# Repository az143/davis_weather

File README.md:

this repository contains all tools necessary for building remote AND online
weather stations using davis vantage vue (or vantage pro) kit.

to be precise, this includes:

* an implementation of the workaround for the infamous "green dot" vendor
lock-in, written in C for a Microchip pic16f88 (without any external
components),

* a data gatherer program (in perl) that fetches the weather readings from a
davis console at configurable intervals, then condenses and uploads the
data to a server on the net,

* a data collector program (in perl) that listens for such uploads and saves the
data in an sqlite database, and optionally uploads it to weather underground
and/or the bom/uk-metoffice weather observations website,

* and a graph generator tool (using gnuplot) and a cgi script to
present readings and graphs. both are written in perl.

there is a little bit of extra documentation on my site at
[http://snafu.priv.at/mystuff/fidobeagle.html](http://snafu.priv.at/mystuff/fidobeagle.html).

all code is (c) 2015 Alexander Zangerl <az@snafu.priv.at>,
and is free and open-source software, licensed under the GPL Version 2.

share and enjoy `:-)`

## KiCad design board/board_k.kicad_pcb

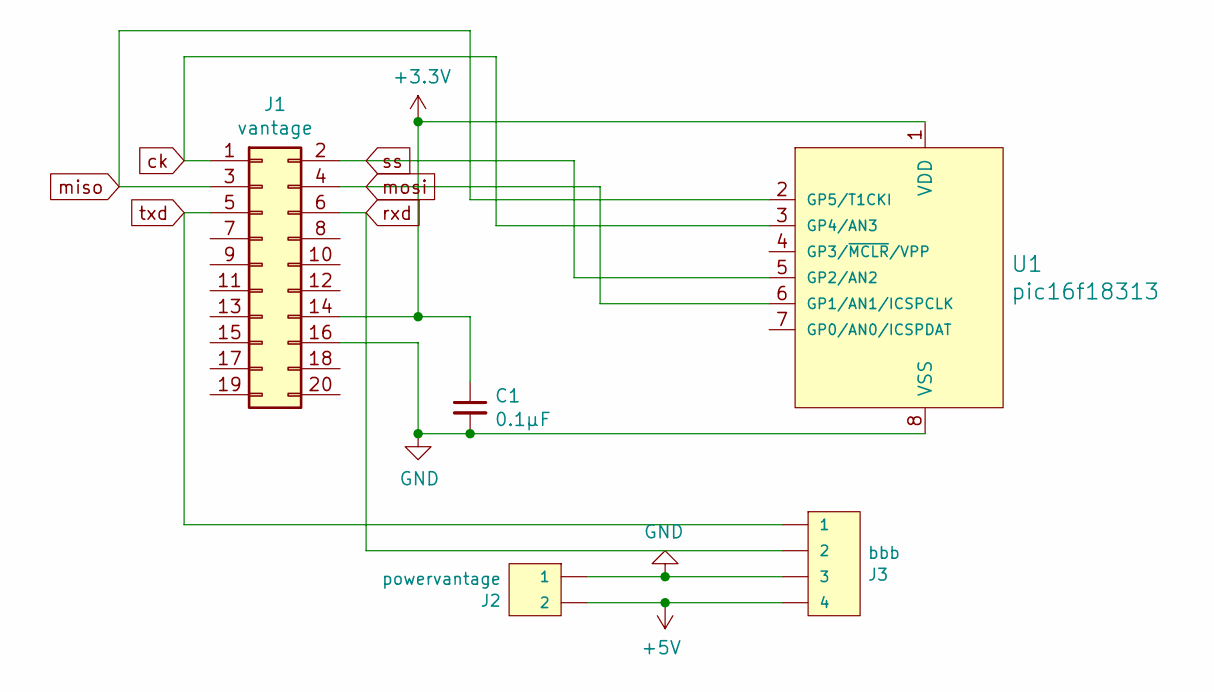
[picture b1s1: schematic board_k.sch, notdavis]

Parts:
C1: 0.1µF; C_Rect_L7.0mm_W3.5mm_P5.00mm
J1: vantage; PinSocket_2x10_P2.00mm_Vertical_SMD
J2: powervantage; JST_XH_B02B-XH-A_1x02_P2.50mm_Vertical
J3: bbb; JST_XH_S04B-XH-A_1x04_P2.50mm_Horizontal
U1: pic16f18313; DIP-8_W7.62mm; MPN PIC12F675-I/P; Digi-Key_PN PIC12F675-I/P-ND

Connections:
+3V3: C1.1, J1.14, U1.1 (VDD)
+5V: J2.2, J3.4
GND: C1.2, J1.16, J2.1, J3.3, U1.8 (VSS)
ck: J1.1, U1.3 (GP4/AN3)
miso: J1.3, U1.2 (GP5/T1CKI)
mosi: J1.4, U1.6 (GP1/AN1/ICSPCLK)
rxd: J1.6, J3.2
ss: J1.2, U1.5 (GP2/AN2)
txd: J1.5, J3.1

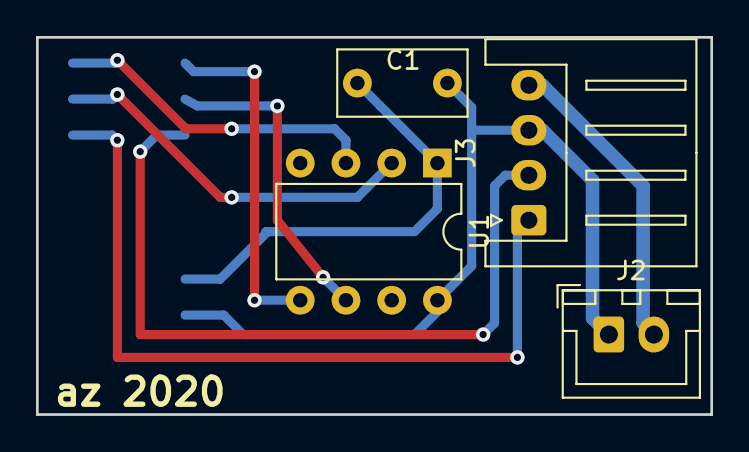
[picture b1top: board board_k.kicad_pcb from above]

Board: 2 copper layers, 37.5 x 21.0 mm, 5 parts (1 on the bottom side), 9 nets.

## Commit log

2015-11-04 initial publication
2015-11-04 added info re upload to wow and wunderground
2015-11-13 reworked cgi layout a bit, added "daily rain last 14 days" to the tables and to the graphs, updated weatherreceiver to export just the daily rain totals with -R
2016-03-05 added polar windrose graph (needs gnuplot 4.6 or newer)
2016-03-13 updated graph generator for better error output, added windrose graph to weather_cgi
2016-12-01 added dynamic display of links to upload sites (wow and wunderground for now)
2018-09-12 updated xc8 args and clean for newer version (1.45, not ancient 1.12)
2018-10-01 updated for more modern (and cheaper...) pic16f18313
2018-10-28 added board for pic16f18313 implementation
2019-12-16 fetchdavis: applied two patches by Bernhard Reutner-Fischer to handle certain errors and corner cases more robustly
2020-08-26 made new board in kicad (2-layer, too lazy to do more toner transfers...) checkin contains gerber & drill files
